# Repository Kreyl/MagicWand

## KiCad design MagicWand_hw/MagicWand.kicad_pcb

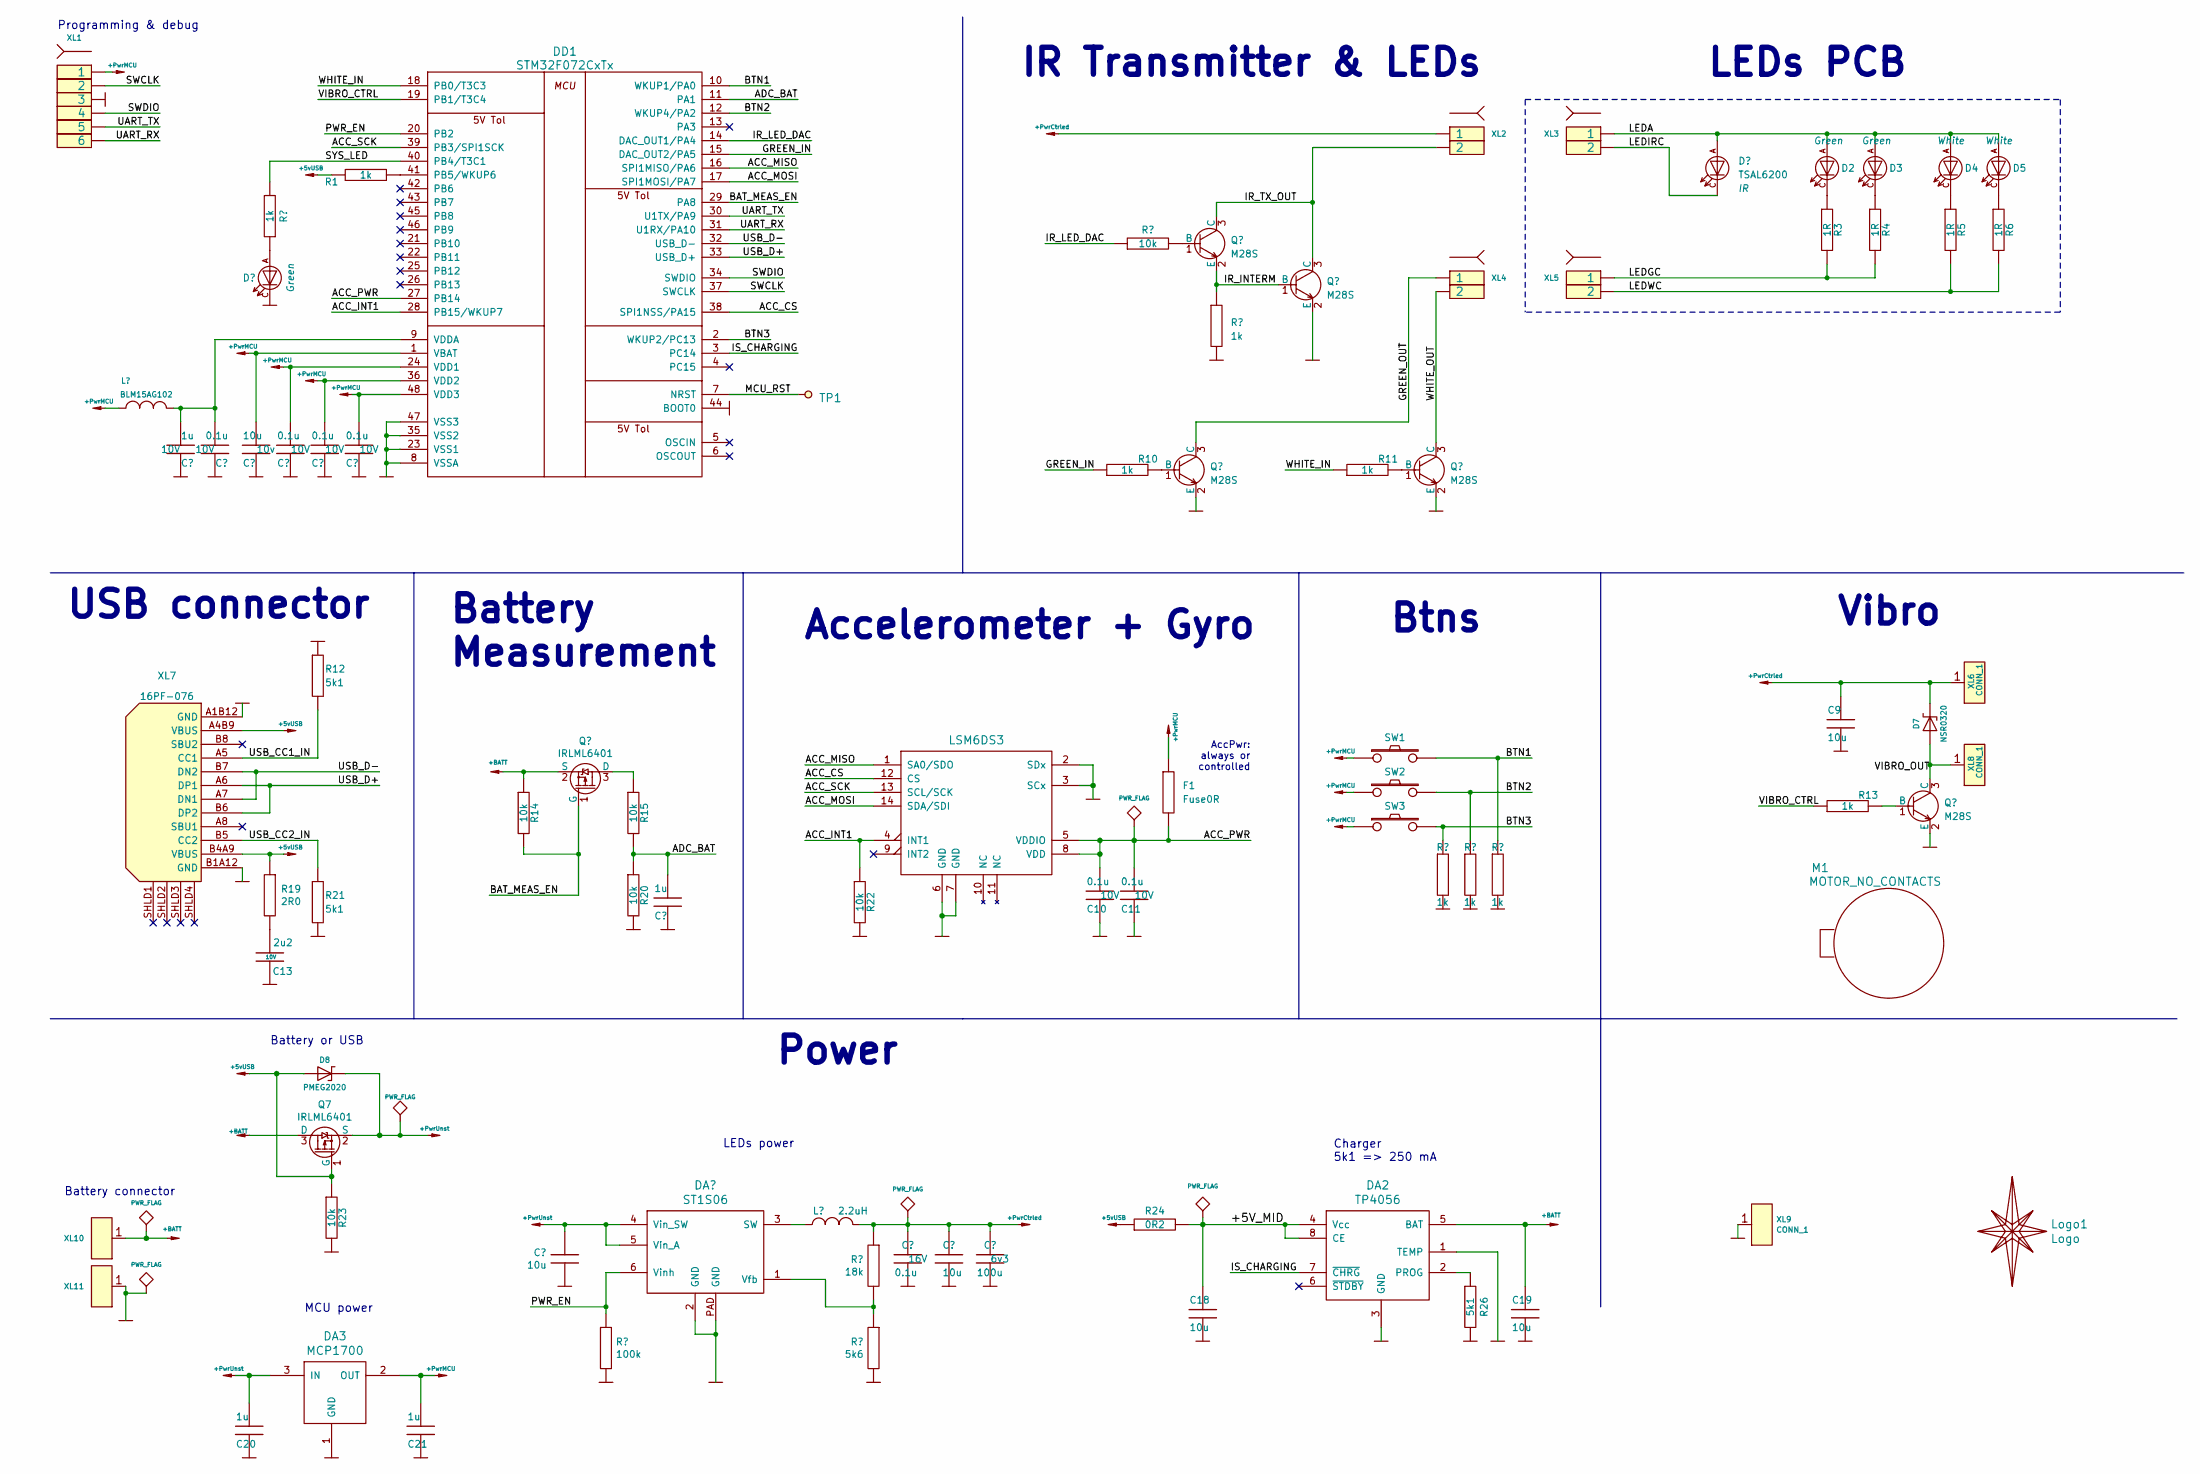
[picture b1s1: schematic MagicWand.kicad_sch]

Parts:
C2: 1u; CAP_0603_Silks; Tolerance 10%; Voltage 10V
C3, C5, C6, C7, C10, C11: 0.1u; CAP_0603_Silks; Tolerance 20%; Voltage 10V
C4: 10u; CAP_0603_Silks; Tolerance 20%; Voltage 10v
C9, C14, C16, C18, C19: 10u; CAP_0603_Silks
C12, C20, C21: 1u; CAP_0603_Silks
C13: 2u2; CAP_0603_Silks; Tolerance 20%; Voltage 10V
C15: 0.1u; CAP_0603_Silks; Tolerance 10%; Voltage 16V
C17: 100u; CAP_1206; Tolerance 10%; Voltage 6v3
D1: TSAL6200; LED_Through-Hole-3mm-Angle
D2, D3, D4, D5: 2835; LED_PLCC2835
D6: LED; LED_0603
D7: NSR0320; SOD323
D8: PMEG2020; SOD323
DA1: ST1S06; DFN6_3x3
DA2: TP4056; SO8_150MIL
DA3: MCP1700; SOT23-3A
DD1: STM32F072CxTx; LQFP48
DD2: LSM6DS3; 14_3x2d5_p0d5
F1: Fuse0R; RES_0603_FUSE
L1: BLM15AG102; IND_0402_Fab; Tolerance 20%
L2: 2.2uH; IND_SRN2512
Logo1: Logo; Ostranna_12d7_10d1
M1: MOTOR_NO_CONTACTS; Motor_no_Contacts10mm
Q1, Q2, Q3, Q4, Q6: M28S; SOT23-3
Q5, Q7: IRLML6401; SOT23-3
R1, R10, R11, R13: 1k; RES_0603_Silks
R2, R8, R16, R17, R18: 1k; RES_0603_Silks; Tolerance 1%
R3, R4, R5, R6: 1R; RES_0603_Silks; Tolerance 1%
R7, R14, R15, R20, R22, R23: 10k; RES_0603_Silks; Tolerance 1%
R12, R21: 5k1; RES_0603_Silks; Tolerance 1%
R19: 2R0; RES_0603_Silks; Tolerance 1%
R24: 0R2; RES_0603_Silks
R25: 18k; RES_0603_Silks
R26: 5k1; RES_0603_Silks
R27: 100k; RES_0603_Silks
R28: 5k6; RES_0603_Silks
SW1, SW2, SW3: BUTTON; BTN_4x4_SMD
TP1: TESTPOINT; TESTPOINT_1MM
XL1: SOCKET_6; PLS-6-NoHole
XL2, XL3, XL4, XL5: SOCKET_2; SLD_2_2D5_SMD
XL6, XL8: CONN_1; Oval3x1.5
XL7: 16PF-076; USBC_16PF-076
XL9: CONN_1; PLS-1Rnd
XL10: CONN_1; PLS-1Oval
XL11: CONN_1; PLS-1Rect

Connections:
+5vUSB: D8.A, Q7.1 (G), R1.2, R19.1, R23.1, R24.1, XL7.A4B9 (VBUS), XL7.B4A9 (VBUS)
+BATT: C19.2, DA2.5 (BAT), Q5.2 (S), Q7.3 (D), R14.1, XL10.1
+PwrCtrled: C9.2, C15.1, C16.1, C17.1, D7.C, L2.2, R25.1, XL2.1, XL6.1
+PwrMCU: C4.1, C5.1, C6.1, C7.1, C21.1, DA3.2 (OUT), DD1.1 (VBAT), DD1.24 (VDD1), DD1.36 (VDD2), DD1.48 (VDD3), F1.1, L1.2, SW1.1, SW2.1, SW3.1, XL1.1
+PwrUnst: C14.1, C20.1, D8.C, DA1.4 (Vin_SW), DA1.5 (Vin_A), DA3.3 (IN), Q7.2 (S)
/+5V_MID: C18.2, DA2.4 (Vcc), DA2.8 (CE), R24.2
/ACC_CS: DD1.38 (SPI1NSS/PA15), DD2.12 (CS)
/ACC_INT1: DD1.28 (PB15/WKUP7), DD2.4 (INT1), R22.1
/ACC_MISO: DD1.16 (SPI1MISO/PA6), DD2.1 (SA0/SDO)
/ACC_MOSI: DD1.17 (SPI1MOSI/PA7), DD2.14 (SDA/SDI)
/ACC_PWR: C10.1, C11.1, DD1.27 (PB14), DD2.5 (VDDIO), DD2.8 (VDD), F1.2
/ACC_SCK: DD1.39 (PB3/SPI1SCK), DD2.13 (SCL/SCK)
/ADC_BAT: C12.1, DD1.11 (PA1), R15.2, R20.1
/BAT_MEAS_EN: DD1.29 (PA8), Q5.1 (G), R14.2
/BTN1: DD1.10 (WKUP1/PA0), R18.1, SW1.2
/BTN2: DD1.12 (WKUP4/PA2), R17.1, SW2.2
/BTN3: DD1.2 (WKUP2/PC13), R16.1, SW3.2
/GREEN_IN: DD1.15 (DAC_OUT2/PA5), R10.1
/GREEN_OUT: Q3.3 (C), XL4.1
/IR_INTERM: Q1.2 (E), Q2.1 (B), R8.1
/IR_LED_DAC: DD1.14 (DAC_OUT1/PA4), R7.1
/IR_TX_OUT: Q1.3 (C), Q2.3 (C), XL2.2
/IS_CHARGING: DA2.7 (~CHRG), DD1.3 (PC14)
/LEDA: D1.A, D2.A, D3.A, D4.A, D5.A, XL3.1
/LEDGC: R3.2, R4.2, XL5.1
/LEDIRC: D1.C, XL3.2
/LEDWC: R5.2, R6.2, XL5.2
/MCU_RST: DD1.7 (NRST), TP1.1
/PWR_EN: DA1.6 (Vinh), DD1.20 (PB2), R27.1
/SWCLK: DD1.37 (SWCLK), XL1.2
/SWDIO: DD1.34 (SWDIO), XL1.4
/SYS_LED: DD1.40 (PB4/T3C1), R2.2
/UART_RX: DD1.31 (U1RX/PA10), XL1.6
/UART_TX: DD1.30 (U1TX/PA9), XL1.5
/USB_CC1_IN: R12.2, XL7.A5 (CC1)
/USB_CC2_IN: R21.1, XL7.B5 (CC2)
/USB_D+: DD1.33 (USB_D+), XL7.A6 (DP1), XL7.B6 (DP2)
/USB_D-: DD1.32 (USB_D-), XL7.A7 (DN1), XL7.B7 (DN2)
/VIBRO_CTRL: DD1.19 (PB1/T3C4), R13.1
/VIBRO_OUT: D7.A, Q6.3 (C), XL8.1
/WHITE_IN: DD1.18 (PB0/T3C3), R11.1
/WHITE_OUT: Q4.3 (C), XL4.2
GND: C2.2, C3.2, C4.2, C5.2, C6.2, C7.2, C9.1, C10.2, C11.2, C12.2, C13.2, C14.2, C15.2, C16.2, C17.2, C18.1, C19.1, C20.2, C21.2, D6.C, DA1.2 (GND), DA1.PAD (GND), DA2.1 (TEMP), DA2.3 (GND), DA3.1 (GND), DD1.8 (VSSA), DD1.23 (VSS1), DD1.35 (VSS2), DD1.44 (BOOT0), DD1.47 (VSS3), DD2.2 (SDx), DD2.3 (SCx), DD2.6 (GND), DD2.7 (GND), Q2.2 (E), Q3.2 (E), Q4.2 (E), Q6.2 (E), R8.2, R12.1, R16.2, R17.2, R18.2, R20.2, R21.2, R22.2, R23.2, R26.2, R27.2, R28.2, XL1.3, XL7.A1B12 (GND), XL7.B1A12 (GND), XL9.1, XL11.1
unnamed: C13.1, R19.2
unnamed: D2.C, R3.1
unnamed: D3.C, R4.1
unnamed: D4.C, R5.1
unnamed: D5.C, R6.1
unnamed: D6.A, R2.1
unnamed: DA1.3 (SW), L2.1
unnamed: DA1.1 (Vfb), R25.2, R28.1
unnamed: DA2.2 (PROG), R26.1
unnamed: DD1.41 (PB5/WKUP6), R1.1
unnamed: C2.1, C3.1, DD1.9 (VDDA), L1.1
unnamed: Q1.1 (B), R7.2
unnamed: Q3.1 (B), R10.2
unnamed: Q4.1 (B), R11.2
unnamed: Q5.3 (D), R15.1
unnamed: Q6.1 (B), R13.2

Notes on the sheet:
Power
Battery Measurement
Programming & debug
Btns
LEDs power
IR Transmitter & LEDs
Accelerometer + Gyro
Battery connector
MCU power
Charger 5k1 => 250 mA
USB connector
Vibro
Battery or USB
LEDs PCB
AccPwr: always or controlled

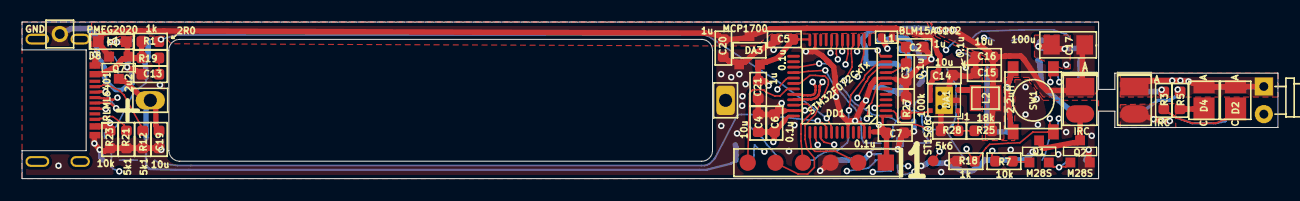
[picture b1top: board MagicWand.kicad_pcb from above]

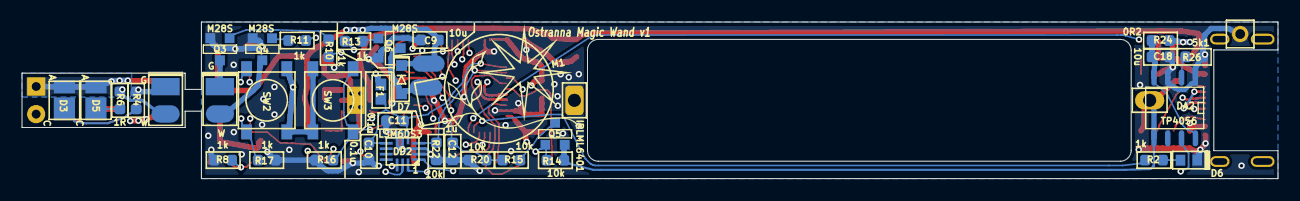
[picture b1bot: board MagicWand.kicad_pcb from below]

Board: 4 copper layers, 115.5 x 14.4 mm, 86 parts (40 on the bottom side), 59 nets.

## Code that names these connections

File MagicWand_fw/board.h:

/*
 * board.h
 *
 *  Created on: 01.02.2017
 *      Author: Kreyl
 */

#pragma once

// ==== General ====
#define BOARD_NAME          "MagicWandPcb1"
#define APP_NAME            "MagicWand"

// MCU type as defined in the ST header.
#define STM32F072xB     // no matter, 8 or B

// Freq of external crystal if any. Leave it here even if not used.
#define CRYSTAL_FREQ_HZ         12000000

// Ch timer
#define STM32_ST_IRQ_PRIORITY   2
#define STM32_ST_USE_TIMER      14
#define SYS_TIM_CLK             (Clk.APBFreqHz)

#define SIMPLESENSORS_ENABLED   FALSE
#define BUTTONS_ENABLED         FALSE
#define ADC_REQUIRED            FALSE
#define I2C1_ENABLED            FALSE
#define I2C_USE_SEMAPHORE       FALSE

// Flash
#define FLASH_START_ADDR        0x08000000UL
#define FW_BOOT_SZ              0x2000UL // 8192
#define FW_START_ADDR           (FLASH_START_ADDR + FW_BOOT_SZ)
#define FW_MAX_SZ               0xD000UL // 53248, about half of (128 total - 2 settings - 8 bootloader)
#define FW_PARAMS_ADDR          (FW_START_ADDR + FW_MAX_SZ)
#define FW_PARAMS_SZ            2048UL // PageSz
#define FW_STORAGE_ADDR         (FW_PARAMS_ADDR + FW_PARAMS_SZ)
#define SETTINGS_STORAGE_ADDR   0x0801F800UL // 128k - 2k, where 2k is Flash Page size

#if 1 // ========================== GPIO =======================================
// PortMinTim_t: GPIO, Pin, Tim, TimChnl, invInverted, omPushPull, TopValue

// UART
#define UART_GPIO       GPIOA
#define UART_TX_PIN     9
#define UART_RX_PIN     10

// Buttons
#define BTN1_PIN        GPIOA, 0,  pudPullDown // WKUP1
#define BTN2_PIN        GPIOA, 2,  pudPullDown // WKUP4
#define BTN3_PIN        GPIOC, 13, pudPullDown // WKUP2

// LEDs
#define SYS_LED         { GPIOB, 4, TIM3, 1, invNotInverted, omPushPull, 255 }
#define LUMOS_LED       { GPIOB, 0, TIM3, 3, invNotInverted, omPushPull, 255 }
#define GREEN_LED       GPIOA, 5 // DAC2
#define LED_PWR_EN      GPIOB, 2

// IR LED
#define IR_LED          GPIOA, 4 // DAC1
#define IR_CARRIER_HZ   38000UL
#define IR_BIT_CNT_MAX  16L     // Just for buffer reservation

// ADC
#define ADC_BAT_IN      GPIOA, 1
#define ADC_BATMEAS_EN  GPIOA, 8

// Accelerometer
#define ACC_MISO        GPIOA, 6
#define ACC_MOSI        GPIOA, 7
#define ACC_CS          GPIOA, 15
#define ACC_SCK         GPIOB, 3
#define ACC_PWR         GPIOB, 14
#define ACC_INT1        GPIOB, 15 // WKUP7

// USB
#define USB_DETECT_PIN  GPIOB, 5 // WKUP6
#define USB_DM          GPIOA, 11
#define USB_DP          GPIOA, 12

// Others
#define IS_CHARGING_PIN GPIOC, 14
#define VIBRO_PIN       { GPIOB, 1, TIM3, 4, invNotInverted, omPushPull, 255 }

#endif // GPIO

#if 1 // ========================= Timer =======================================
// IR LED
#define TMR_DAC_SMPL    TIM7
// IR Receiver
#define TMR_IR_RX       TIM15
#define TMR_IR_RX_IRQ   TIM15_IRQn
#define TMR_IR_RX_IRQ_HNDLR   Vector90
#endif // Timer

#if 1 // =========================== DMA =======================================
#define STM32_DMA_REQUIRED  TRUE
// ==== Uart ====
#define UART_DMA_TX_MODE(Chnl) (STM32_DMA_CR_CHSEL(Chnl) | DMA_PRIORITY_LOW | STM32_DMA_CR_MSIZE_BYTE | STM32_DMA_CR_PSIZE_BYTE | STM32_DMA_CR_MINC | STM32_DMA_CR_DIR_M2P | STM32_DMA_CR_TCIE)
#define UART_DMA_RX_MODE(Chnl) (STM32_DMA_CR_CHSEL(Chnl) | DMA_PRIORITY_MEDIUM | STM32_DMA_CR_MSIZE_BYTE | STM32_DMA_CR_PSIZE_BYTE | STM32_DMA_CR_MINC | STM32_DMA_CR_DIR_P2M | STM32_DMA_CR_CIRC)
#define UART_DMA_TX     STM32_DMA_STREAM_ID(1, 2)
#define UART_DMA_RX     STM32_DMA_STREAM_ID(1, 5)
#define UART_DMA_CHNL   0   // Dummy

// === IR TX DAC ====
#define DAC_DMA         STM32_DMA_STREAM_ID(1, 3)
#define DAC_DMA_CHNL    0   // Dummy


#endif // DMA

#if 1 // ========================== USART ======================================
#define PRINTF_FLOAT_EN FALSE
#define UART_TXBUF_SZ   4096
#define UART_RXBUF_SZ   256
#define CMD_BUF_SZ      256

#define CMD_UART        USART1


#define CMD_UART_PARAMS \
    CMD_UART, UART_GPIO, UART_TX_PIN, UART_GPIO, UART_RX_PIN, \
    UART_DMA_TX, UART_DMA_RX, UART_DMA_TX_MODE(UART_DMA_CHNL), UART_DMA_RX_MODE(UART_DMA_CHNL), \
    uartclkHSI // independent clock

#endif

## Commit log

2024-01-28 PCB layout done
2024-01-28 Remove quartz, PCB length decreased to 99mm
2024-01-31 USB conn changed to real one
2024-01-31 PCB sent to factory
2024-02-12 + Starting firmware dev
2024-02-17 + Lumos, Avada, sleep & wake
2024-02-17 + Serial USB + UsbDetect + Charging
2024-02-17 + FW update works
2024-02-18 + Full hex added
